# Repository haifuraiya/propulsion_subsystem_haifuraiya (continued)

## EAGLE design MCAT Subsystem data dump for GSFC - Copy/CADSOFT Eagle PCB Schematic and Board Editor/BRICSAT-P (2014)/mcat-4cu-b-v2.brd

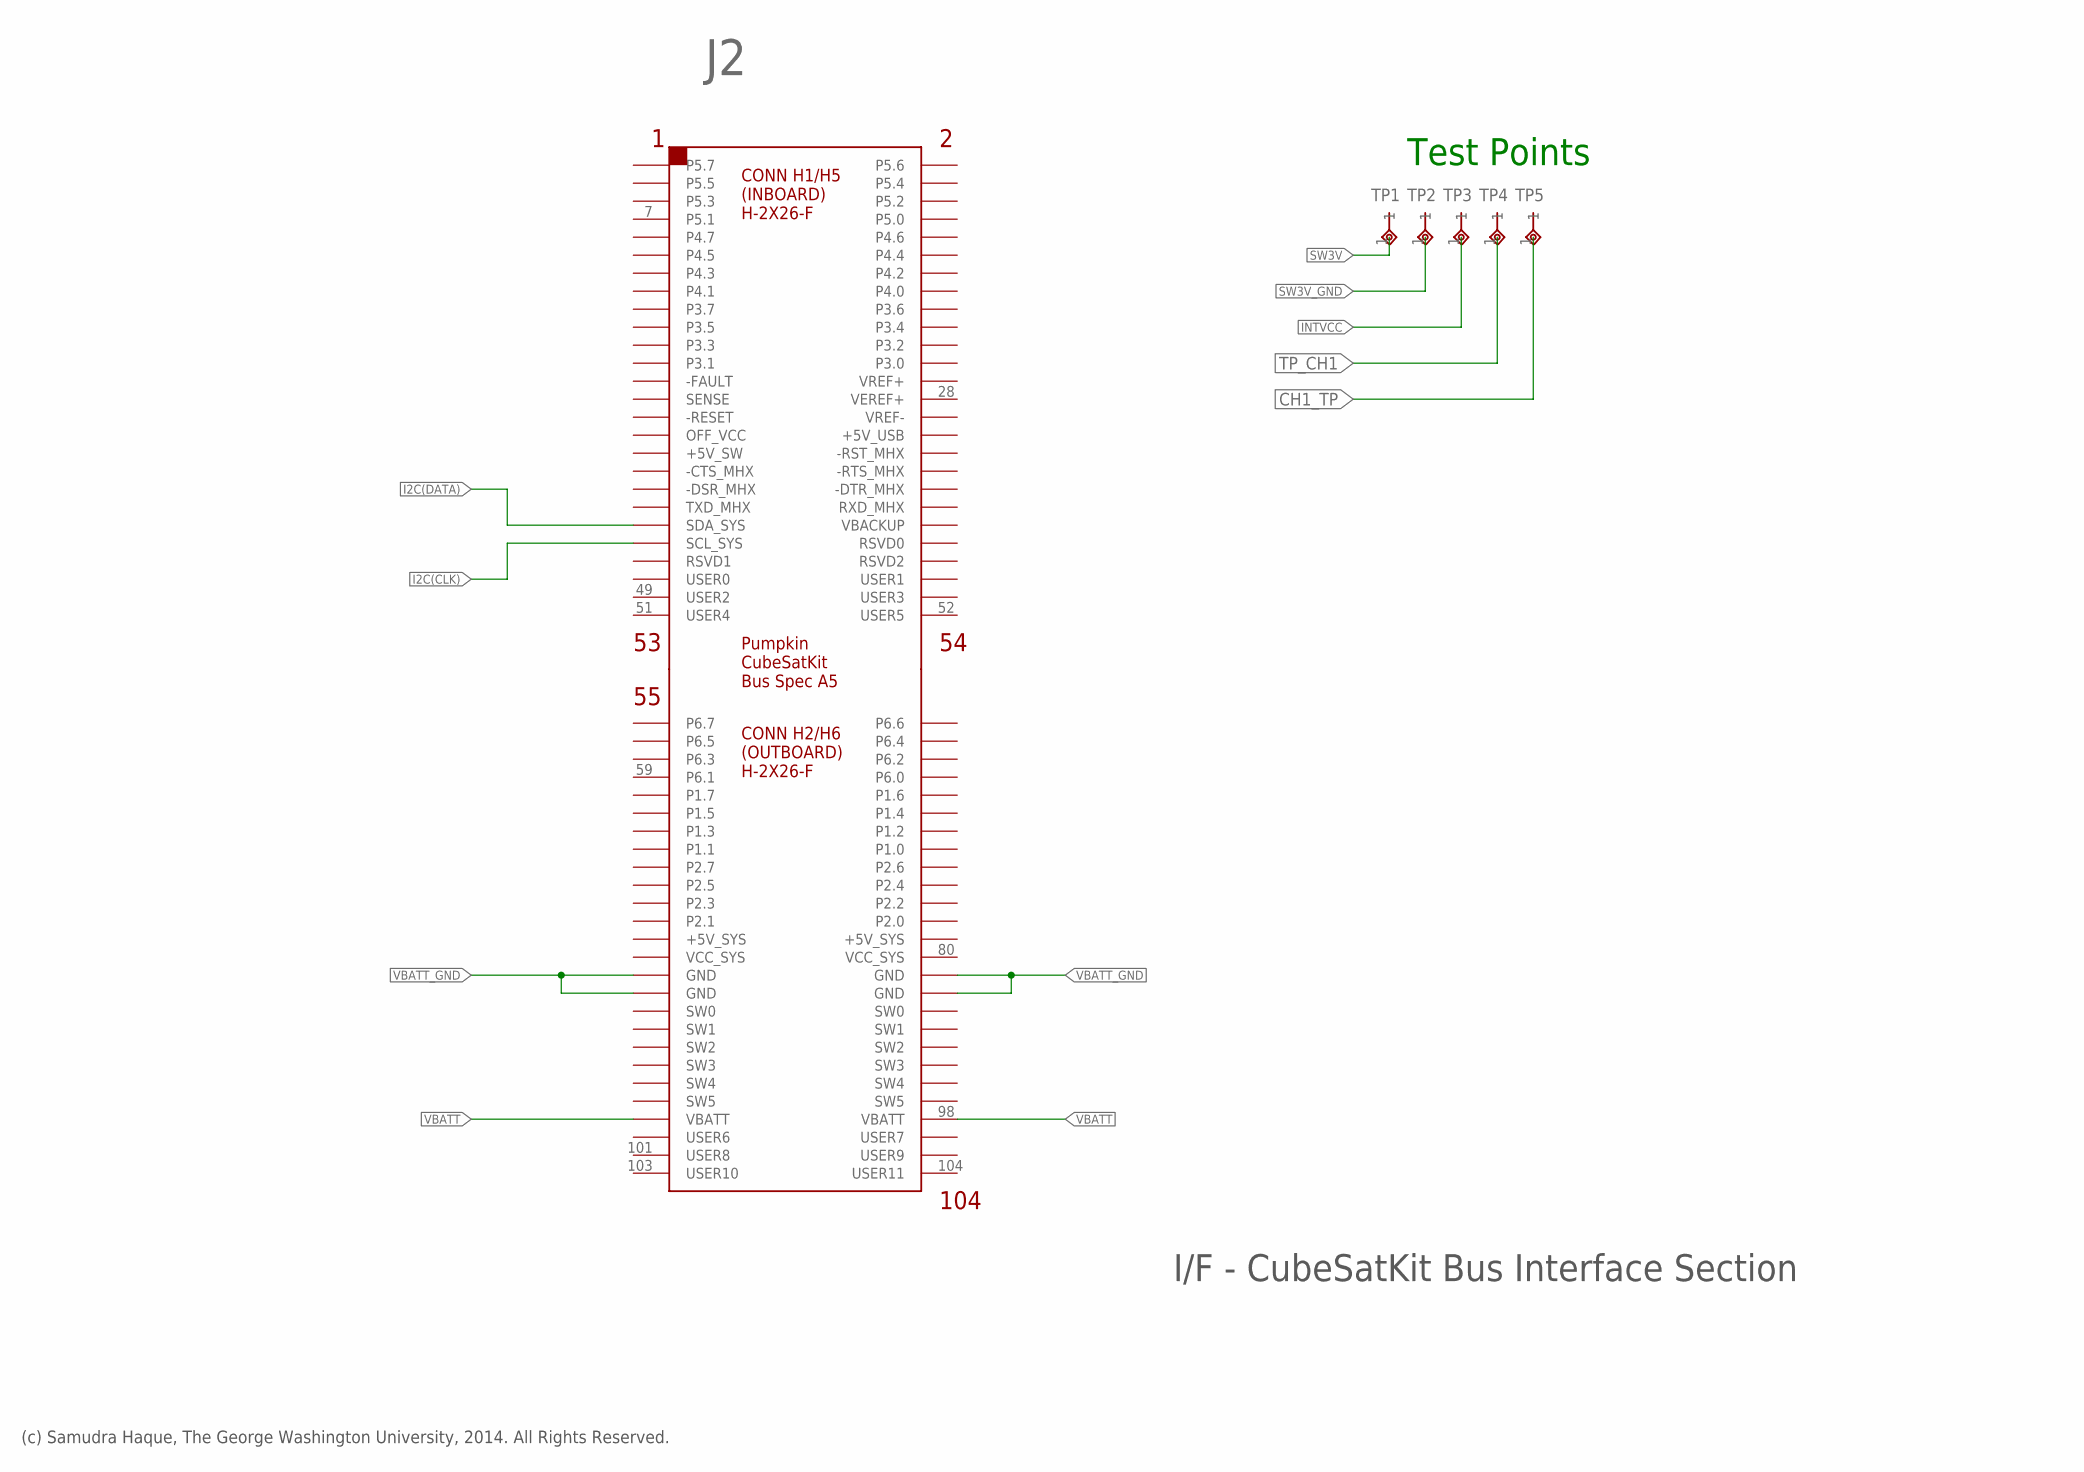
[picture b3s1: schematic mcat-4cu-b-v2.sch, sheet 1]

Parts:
J2: CSK-BUS-CONN2X2X26; CSK-BUS-PKG
TP1, TP2, TP3, TP4, TP5: 1P-1508-0-57-15-00-00-03-0; 1P-TP-MILLMAX-11

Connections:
CH1_TP: TP5.1; also elsewhere on the board
I2C(CLK): J2.43 (SCL_SYS); also elsewhere on the board
I2C(DATA): J2.41 (SDA_SYS); also elsewhere on the board
INTVCC: TP3.1; also elsewhere on the board
SW3V: TP1.1; also elsewhere on the board
SW3V_GND: TP2.1; also elsewhere on the board
TP_CH1: TP4.1; also elsewhere on the board
VBATT: J2.97 (VBATT), J2.98 (VBATT); also elsewhere on the board
VBATT_GND: J2.81 (GND), J2.82 (GND), J2.83 (GND), J2.84 (GND); also elsewhere on the board

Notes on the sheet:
I/F - CubeSatKit Bus Interface Section
Test Points
(c) Samudra Haque, The George Washington University, 2014. All Rights Reserved.

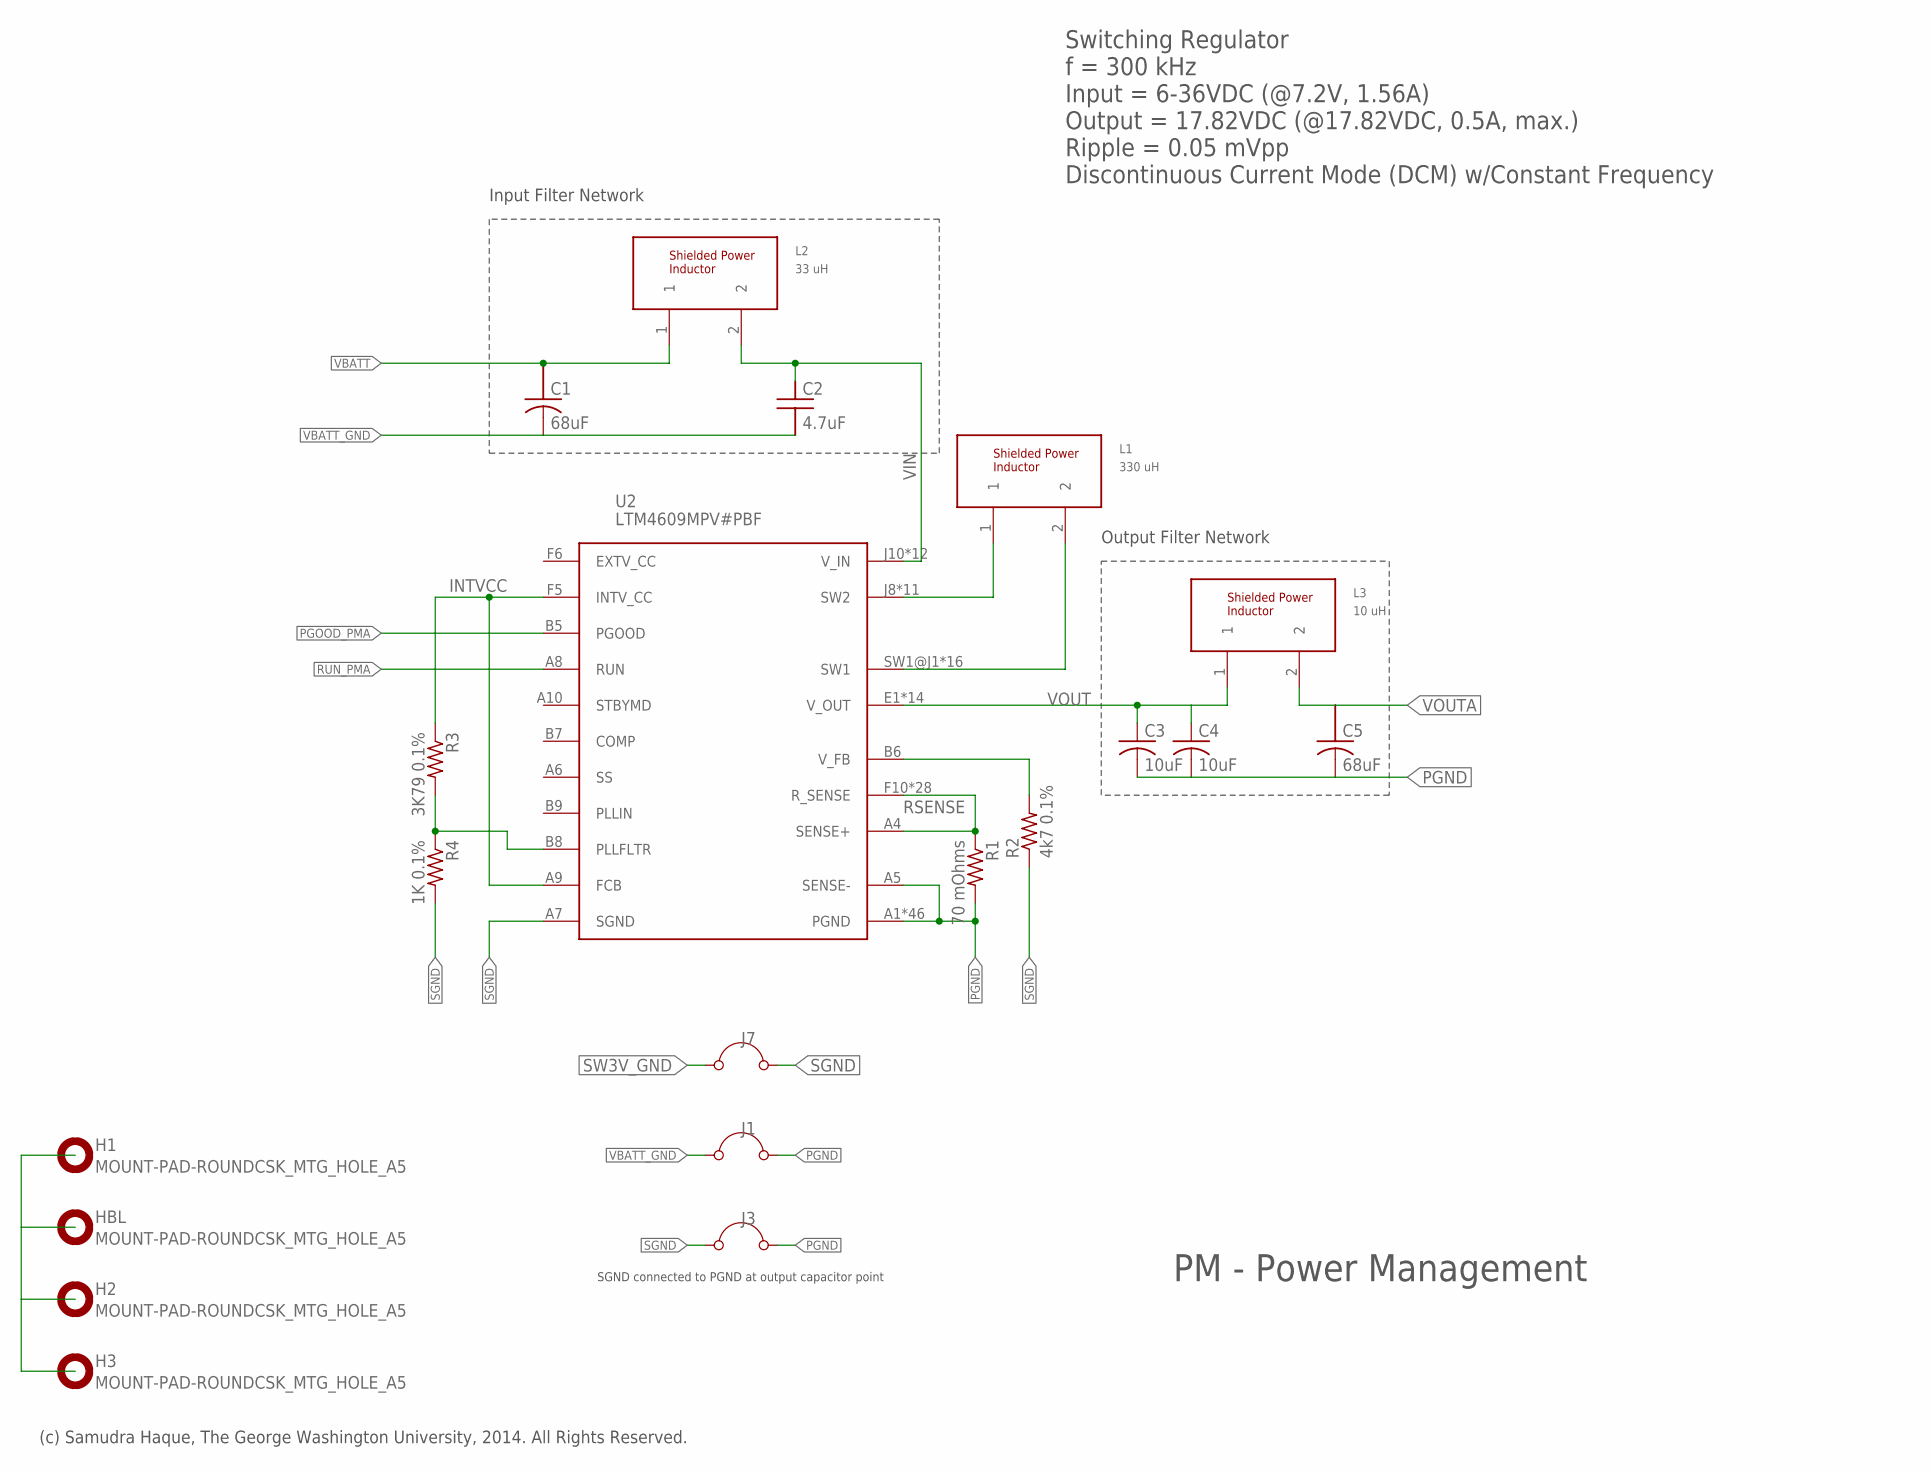
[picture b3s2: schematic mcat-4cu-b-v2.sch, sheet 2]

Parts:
C1, C5: 68uF; OS-CON-SVPF-F12
C2: 4.7uF; MLCC-X7R-1210
C3, C4: 10uF; C1210K
H1, H2, H3: MOUNT-PAD-ROUNDCSK_MTG_HOLE_A5; CSK_MOUNTING_HOLE
HBL: MOUNT-PAD-ROUNDCSK_MTG_HOLE_A5; CSK_MOUNTING_HOLE
J1, J3, J7: JUMPER; 05
L1: 330 uH; MSS1048
L2: 33 uH; MSS1048
L3: 10 uH; SERIES-POWER-INDUCTORS
R1: 70 mOhms; R1206
R2: 4k7 0.1%; R0603
R3: 3K79 0.1%; R0805
R4: 1K 0.1%; R0805
U2: LTM4609MPV#PBF; LGA-141-LTC-05-08-1840-B

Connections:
INTVCC: R3.1, U2.A9 (FCB), U2.F5 (INTV_CC); also elsewhere on the board
unnamed: R2.2, U2.B6 (V_FB)
unnamed: H1.P$1, H2.P$1, H3.P$1, HBL.P$1
PGND: C3.2, C4.2, C5.K1 (K), J1.2 (-), J3.2 (-), R1.2, U2.A1 (PGND), U2.A2 (PGND), U2.A3 (PGND), U2.A5 (SENSE-), U2.A11 (PGND), U2.A12 (PGND), U2.B1 (PGND), U2.B2 (PGND), U2.B3 (PGND), U2.B4 (PGND), U2.B10 (PGND), U2.B11 (PGND), U2.B12 (PGND), U2.C1 (PGND), U2.C2 (PGND), U2.C3 (PGND), U2.C4 (PGND), U2.C5 (PGND), U2.C6 (PGND), U2.C7 (PGND), U2.C8 (PGND), U2.C9 (PGND), U2.C10 (PGND), U2.C11 (PGND), U2.C12 (PGND), U2.D1 (PGND), U2.D2 (PGND), U2.D3 (PGND), U2.D4 (PGND), U2.D5 (PGND), U2.D6 (PGND), U2.D7 (PGND), U2.D8 (PGND), U2.D9 (PGND), U2.D10 (PGND), U2.D11 (PGND), U2.D12 (PGND), U2.E3 (PGND), U2.E4 (PGND), U2.E5 (PGND), U2.E6 (PGND), U2.E7 (PGND), U2.E8 (PGND), U2.E9 (PGND), U2.E10 (PGND), U2.E11 (PGND), U2.E12 (PGND); also elsewhere on the board
PGOOD_PMA: U2.B5 (PGOOD)
RSENSE: R1.1, U2.A4 (SENSE+), U2.F10 (R_SENSE), U2.F11 (R_SENSE), U2.F12 (R_SENSE), U2.G5 (R_SENSE), U2.G6 (R_SENSE), U2.G7 (R_SENSE), U2.G8 (R_SENSE), U2.G9 (R_SENSE), U2.G10 (R_SENSE), U2.G11 (R_SENSE), U2.G12 (R_SENSE), U2.H5 (R_SENSE), U2.H6 (R_SENSE), U2.H7 (R_SENSE), U2.H8 (R_SENSE), U2.H9 (R_SENSE), U2.H10 (R_SENSE), U2.H11 (R_SENSE), U2.H12 (R_SENSE), U2.J5 (R_SENSE), U2.J6 (R_SENSE), U2.J7 (R_SENSE), U2.K5 (R_SENSE), U2.K6 (R_SENSE), U2.L5 (R_SENSE), U2.L6 (R_SENSE), U2.M5 (R_SENSE), U2.M6 (R_SENSE)
RUN_PMA: U2.A8 (RUN)
SETFREQ: R3.2, R4.1, U2.B8 (PLLFLTR)
SGND: J3.1 (+), J7.2 (-), R2.1, R4.2, U2.A7 (SGND); also elsewhere on the board
SW1: L1.2, U2.SW1@J1 (SW1), U2.SW1@J2 (SW1), U2.SW1@J3 (SW1), U2.SW1@J4 (SW1), U2.SW1@K1 (SW1), U2.SW1@K2 (SW1), U2.SW1@K3 (SW1), U2.SW1@K4 (SW1), U2.SW1@L1 (SW1), U2.SW1@L2 (SW1), U2.SW1@L3 (SW1), U2.SW1@L4 (SW1), U2.SW1@M1 (SW1), U2.SW1@M2 (SW1), U2.SW1@M3 (SW1), U2.SW1@M4 (SW1)
SW2: L1.1, U2.J8 (SW2), U2.J9 (SW2), U2.K7 (SW2), U2.K8 (SW2), U2.K9 (SW2), U2.L7 (SW2), U2.L8 (SW2), U2.L9 (SW2), U2.M7 (SW2), U2.M8 (SW2), U2.M9 (SW2)
SW3V_GND: J7.1 (+); also elsewhere on the board
VBATT: C1.A1 (A), L2.1; also elsewhere on the board
VBATT_GND: C1.K1 (K), C2.2, J1.1 (+); also elsewhere on the board
VIN: C2.1, L2.2, U2.J10 (V_IN), U2.J11 (V_IN), U2.J12 (V_IN), U2.K10 (V_IN), U2.K11 (V_IN), U2.K12 (V_IN), U2.L10 (V_IN), U2.L11 (V_IN), U2.L12 (V_IN), U2.M10 (V_IN), U2.M11 (V_IN), U2.M12 (V_IN)
VOUT: C3.1, C4.1, L3.1, U2.E1 (V_OUT), U2.E2 (V_OUT), U2.F1 (V_OUT), U2.F2 (V_OUT), U2.F3 (V_OUT), U2.F4 (V_OUT), U2.G1 (V_OUT), U2.G2 (V_OUT), U2.G3 (V_OUT), U2.G4 (V_OUT), U2.H2 (V_OUT), U2.H3 (V_OUT), U2.H4 (V_OUT), U2.VOUT (V_OUT)
VOUTA: C5.A1 (A), L3.2; also elsewhere on the board

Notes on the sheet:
PM - Power Management
Input Filter Network
SGND connected to PGND at output capacitor point
Output Filter Network
Switching Regulator f = 300 kHz Input = 6-36VDC (@7.2V, 1.56A) Output = 17.82VDC (@17.82VDC, 0.5A, max.) Ripple = 0.05 mVpp Discontinuous Current Mode (DCM) w/Constant Frequency
(c) Samudra Haque, The George Washington University, 2014. All Rights Reserved.

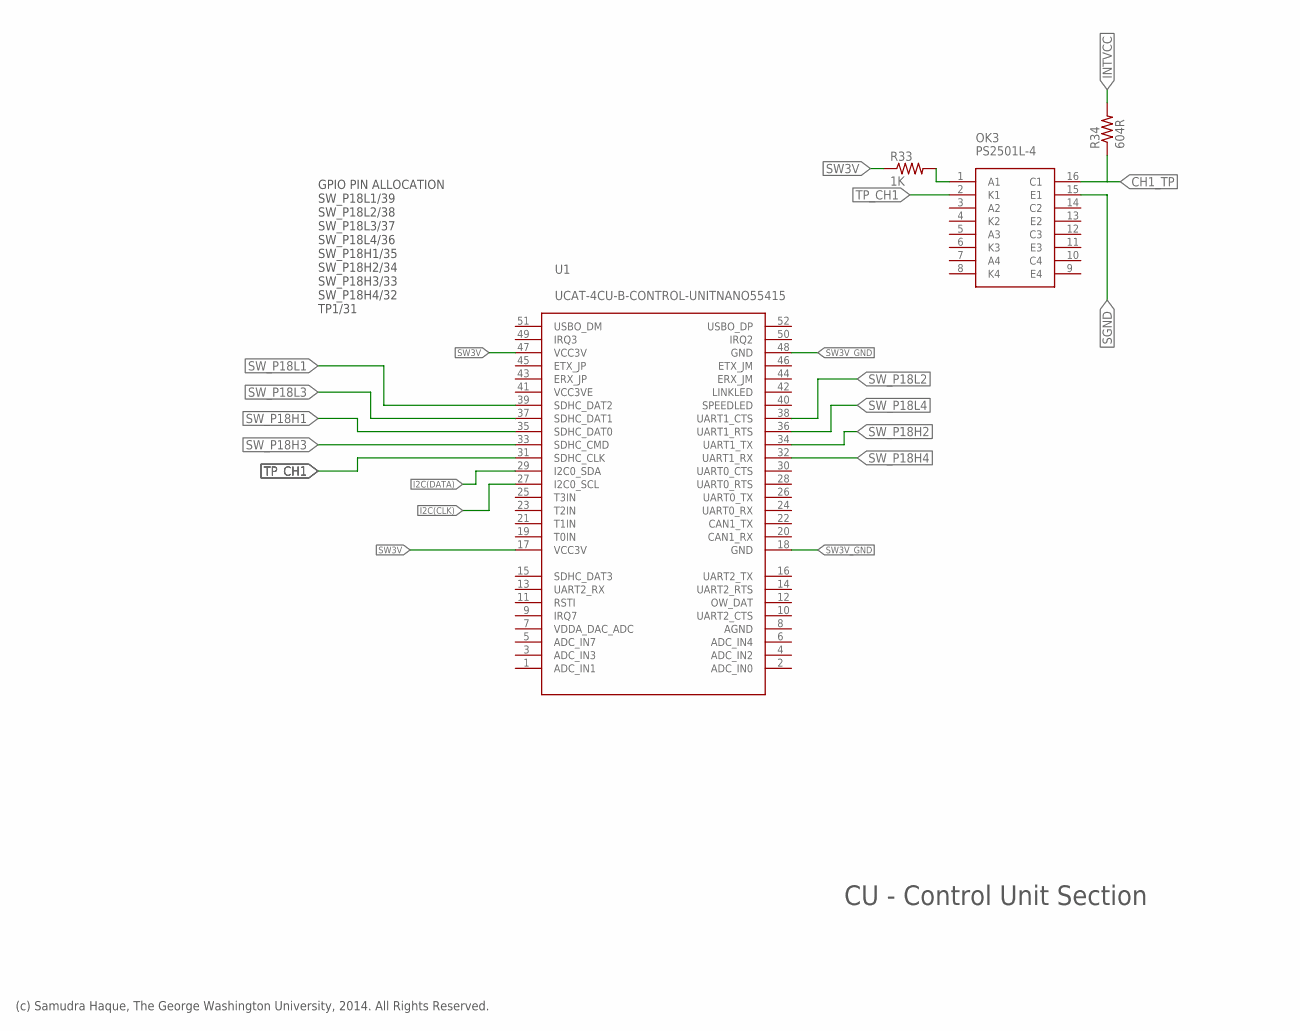
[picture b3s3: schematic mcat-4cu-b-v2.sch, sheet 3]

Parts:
OK3: PS2501L-4
R33: 1K; R0805
R34: 604R; R0805
U1: UCAT-4CU-B-CONTROL-UNITNANO55415; MOLEX-MINI-PCI-EXPRESS-8MM-52CKT

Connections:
CH1_TP: OK3.16 (C1), R34.1; also elsewhere on the board
I2C(CLK): U1.27 (I2C0_SCL); also elsewhere on the board
I2C(DATA): U1.29 (I2C0_SDA); also elsewhere on the board
INTVCC: R34.2; also elsewhere on the board
unnamed: OK3.1 (A1), R33.2
SGND: OK3.15 (E1); also elsewhere on the board
SW3V: R33.1, U1.17 (VCC3V), U1.47 (VCC3V); also elsewhere on the board
SW3V_GND: U1.48 (GND); also elsewhere on the board
SW_P18H1: U1.35 (SDHC_DAT0); also elsewhere on the board
SW_P18H2: U1.34 (UART1_TX); also elsewhere on the board
SW_P18H3: U1.33 (SDHC_CMD); also elsewhere on the board
SW_P18H4: U1.32 (UART1_RX); also elsewhere on the board
SW_P18L1: U1.39 (SDHC_DAT2); also elsewhere on the board
SW_P18L2: U1.38 (UART1_CTS); also elsewhere on the board
SW_P18L3: U1.37 (SDHC_DAT1); also elsewhere on the board
SW_P18L4: U1.36 (UART1_RTS); also elsewhere on the board
TP_CH1: OK3.2 (K1), U1.31 (SDHC_CLK); also elsewhere on the board

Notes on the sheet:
CU - Control Unit Section
GPIO PIN ALLOCATION SW_P18L1/39 SW_P18L2/38 SW_P18L3/37 SW_P18L4/36 SW_P18H1/35 SW_P18H2/34 SW_P18H3/33 SW_P18H4/32 TP1/31
(c) Samudra Haque, The George Washington University, 2014. All Rights Reserved.

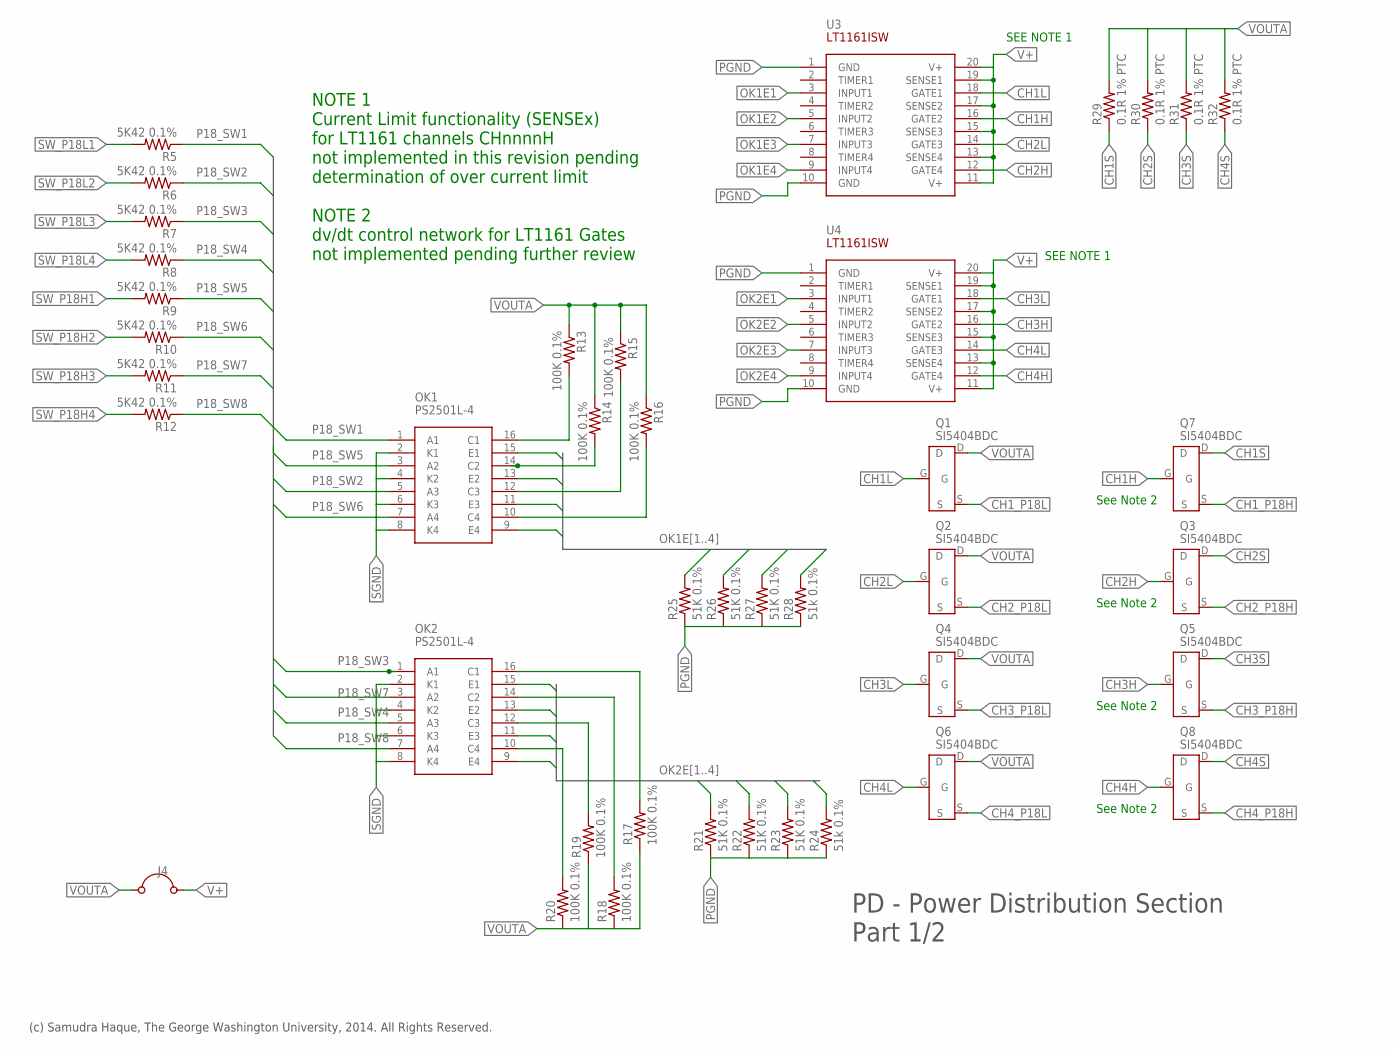
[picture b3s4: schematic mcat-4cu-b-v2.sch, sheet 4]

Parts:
J4: JUMPER; 05
OK1, OK2: PS2501L-4
Q1, Q2, Q3, Q4, Q5, Q6, Q7, Q8: SI5404BDC; 1206-8-CHIPFET
R5, R6, R7, R8, R9, R10, R11, R12: 5K42 0.1%; R1206
R13, R14, R15, R16, R17, R18, R19, R20: 100K 0.1%; R0402
R21, R22, R23, R25, R26, R27: 51K 0.1%; R0603
R24, R28: 51k 0.1%; R0603
R29, R30, R31, R32: 0.1R 1% PTC; R0402
U3, U4: LT1161ISW; 20-LEAD-PLASTIC-SO

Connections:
CH1H: Q7.G, U3.16 (GATE2)
CH1L: Q1.G, U3.18 (GATE1)
CH1S: Q7.D, R29.1
CH1_P18H: Q7.S; also elsewhere on the board
CH1_P18L: Q1.S; also elsewhere on the board
CH2H: Q3.G, U3.12 (GATE4)
CH2L: Q2.G, U3.14 (GATE3)
CH2S: Q3.D, R30.1
CH2_P18H: Q3.S; also elsewhere on the board
CH2_P18L: Q2.S; also elsewhere on the board
CH3H: Q5.G, U4.16 (GATE2)
CH3L: Q4.G, U4.18 (GATE1)
CH3S: Q5.D, R31.1
CH3_P18H: Q5.S; also elsewhere on the board
CH3_P18L: Q4.S; also elsewhere on the board
CH4H: Q8.G, U4.12 (GATE4)
CH4L: Q6.G, U4.14 (GATE3)
CH4S: Q8.D, R32.1
CH4_P18H: Q8.S; also elsewhere on the board
CH4_P18L: Q6.S; also elsewhere on the board
unnamed: OK1.16 (C1), R13.2
unnamed: OK1.14 (C2), R14.2
unnamed: OK1.12 (C3), R15.2
unnamed: OK1.10 (C4), R16.2
unnamed: OK2.16 (C1), R17.2
unnamed: OK2.14 (C2), R18.2
unnamed: OK2.12 (C3), R19.2
unnamed: OK2.10 (C4), R20.2
OK1E1: OK1.15 (E1), R25.2, U3.3 (INPUT1)
OK1E2: OK1.13 (E2), R26.2, U3.5 (INPUT2)
OK1E3: OK1.11 (E3), R27.2, U3.7 (INPUT3)
OK1E4: OK1.9 (E4), R28.2, U3.9 (INPUT4)
OK2E1: OK2.15 (E1), R21.2, U4.3 (INPUT1)
OK2E2: OK2.13 (E2), R22.2, U4.5 (INPUT2)
OK2E3: OK2.11 (E3), R23.2, U4.7 (INPUT3)
OK2E4: OK2.9 (E4), R24.2, U4.9 (INPUT4)
P18_SW1: OK1.1 (A1), R5.1
P18_SW2: OK1.5 (A3), R6.1
P18_SW3: OK2.1 (A1), R7.1
P18_SW4: OK2.5 (A3), R8.1
P18_SW5: OK1.3 (A2), R9.1
P18_SW6: OK1.7 (A4), R10.1
P18_SW7: OK2.3 (A2), R11.1
P18_SW8: OK2.7 (A4), R12.1
PGND: R21.1, R22.1, R23.1, R24.1, R25.1, R26.1, R27.1, R28.1, U3.1 (GND), U3.10 (GND), U4.1 (GND), U4.10 (GND); also elsewhere on the board
SGND: OK1.2 (K1), OK1.4 (K2), OK1.6 (K3), OK1.8 (K4), OK2.2 (K1), OK2.4 (K2), OK2.6 (K3), OK2.8 (K4); also elsewhere on the board
SW_P18H1: R9.2; also elsewhere on the board
SW_P18H2: R10.2; also elsewhere on the board
SW_P18H3: R11.2; also elsewhere on the board
SW_P18H4: R12.2; also elsewhere on the board
SW_P18L1: R5.2; also elsewhere on the board
SW_P18L2: R6.2; also elsewhere on the board
SW_P18L3: R7.2; also elsewhere on the board
SW_P18L4: R8.2; also elsewhere on the board
V+: J4.2 (-), U3.11 (V+), U3.13 (SENSE4), U3.15 (SENSE3), U3.17 (SENSE2), U3.19 (SENSE1), U3.20 (V+), U4.11 (V+), U4.13 (SENSE4), U4.15 (SENSE3), U4.17 (SENSE2), U4.19 (SENSE1), U4.20 (V+)
VOUTA: J4.1 (+), Q1.D, Q2.D, Q4.D, Q6.D, R13.1, R14.1, R15.1, R16.1, R17.1, R18.1, R19.1, R20.1, R29.2, R30.2, R31.2, R32.2; also elsewhere on the board

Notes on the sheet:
PD - Power Distribution Section Part 1/2
NOTE 1 Current Limit functionality (SENSEx) for LT1161 channels CHnnnnH not implemented in this revision pending determination of over current limit NOTE 2 dv/dt control network for LT1161 Gates not implemented pending further review
SEE NOTE 1
See Note 2
(c) Samudra Haque, The George Washington University, 2014. All Rights Reserved.

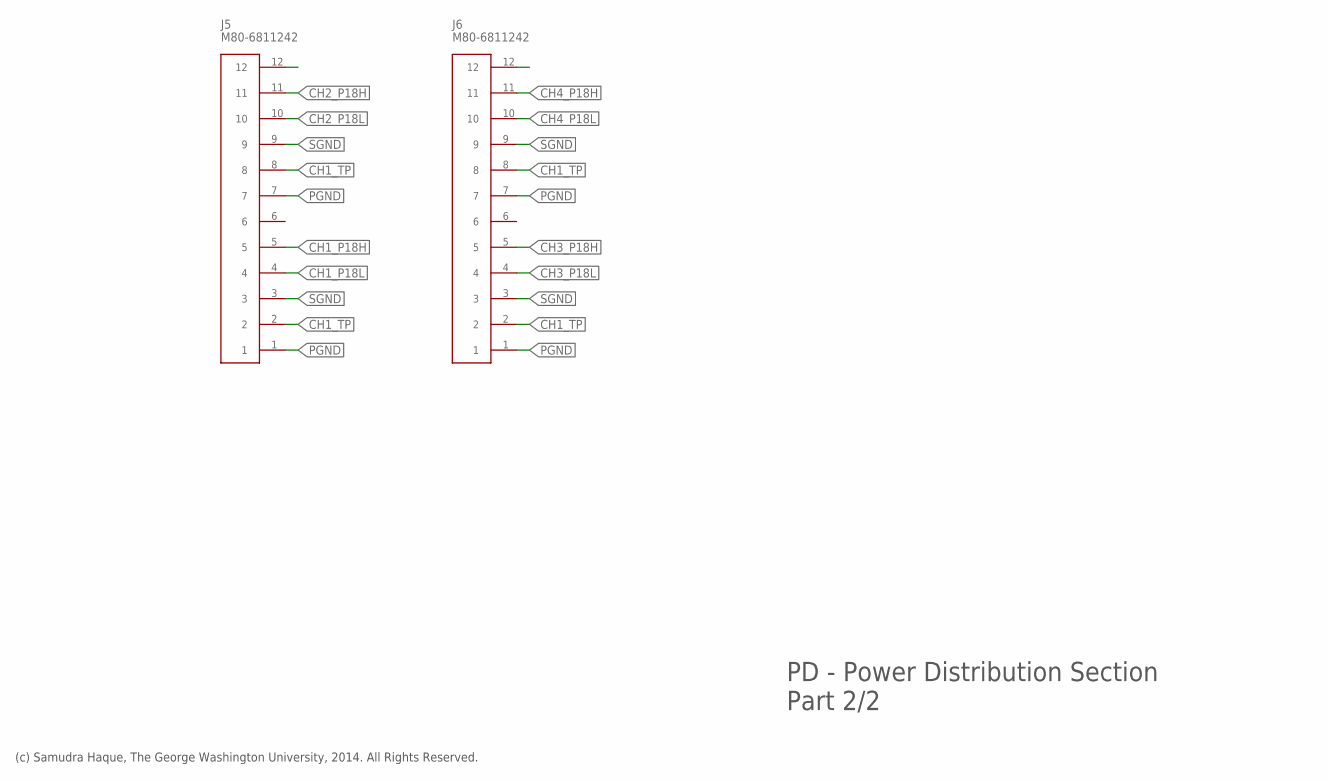
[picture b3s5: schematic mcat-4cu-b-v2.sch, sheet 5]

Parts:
J5, J6: M80-6811242; M80-68112

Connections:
CH1_P18H: J5.5; also elsewhere on the board
CH1_P18L: J5.4; also elsewhere on the board
CH1_TP: J5.2, J5.8, J6.2, J6.8; also elsewhere on the board
CH2_P18H: J5.11; also elsewhere on the board
CH2_P18L: J5.10; also elsewhere on the board
CH3_P18H: J6.5; also elsewhere on the board
CH3_P18L: J6.4; also elsewhere on the board
CH4_P18H: J6.11; also elsewhere on the board
CH4_P18L: J6.10; also elsewhere on the board
PGND: J5.1, J5.7, J6.1, J6.7; also elsewhere on the board
SGND: J5.3, J5.9, J6.3, J6.9; also elsewhere on the board

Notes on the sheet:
PD - Power Distribution Section Part 2/2
(c) Samudra Haque, The George Washington University, 2014. All Rights Reserved.

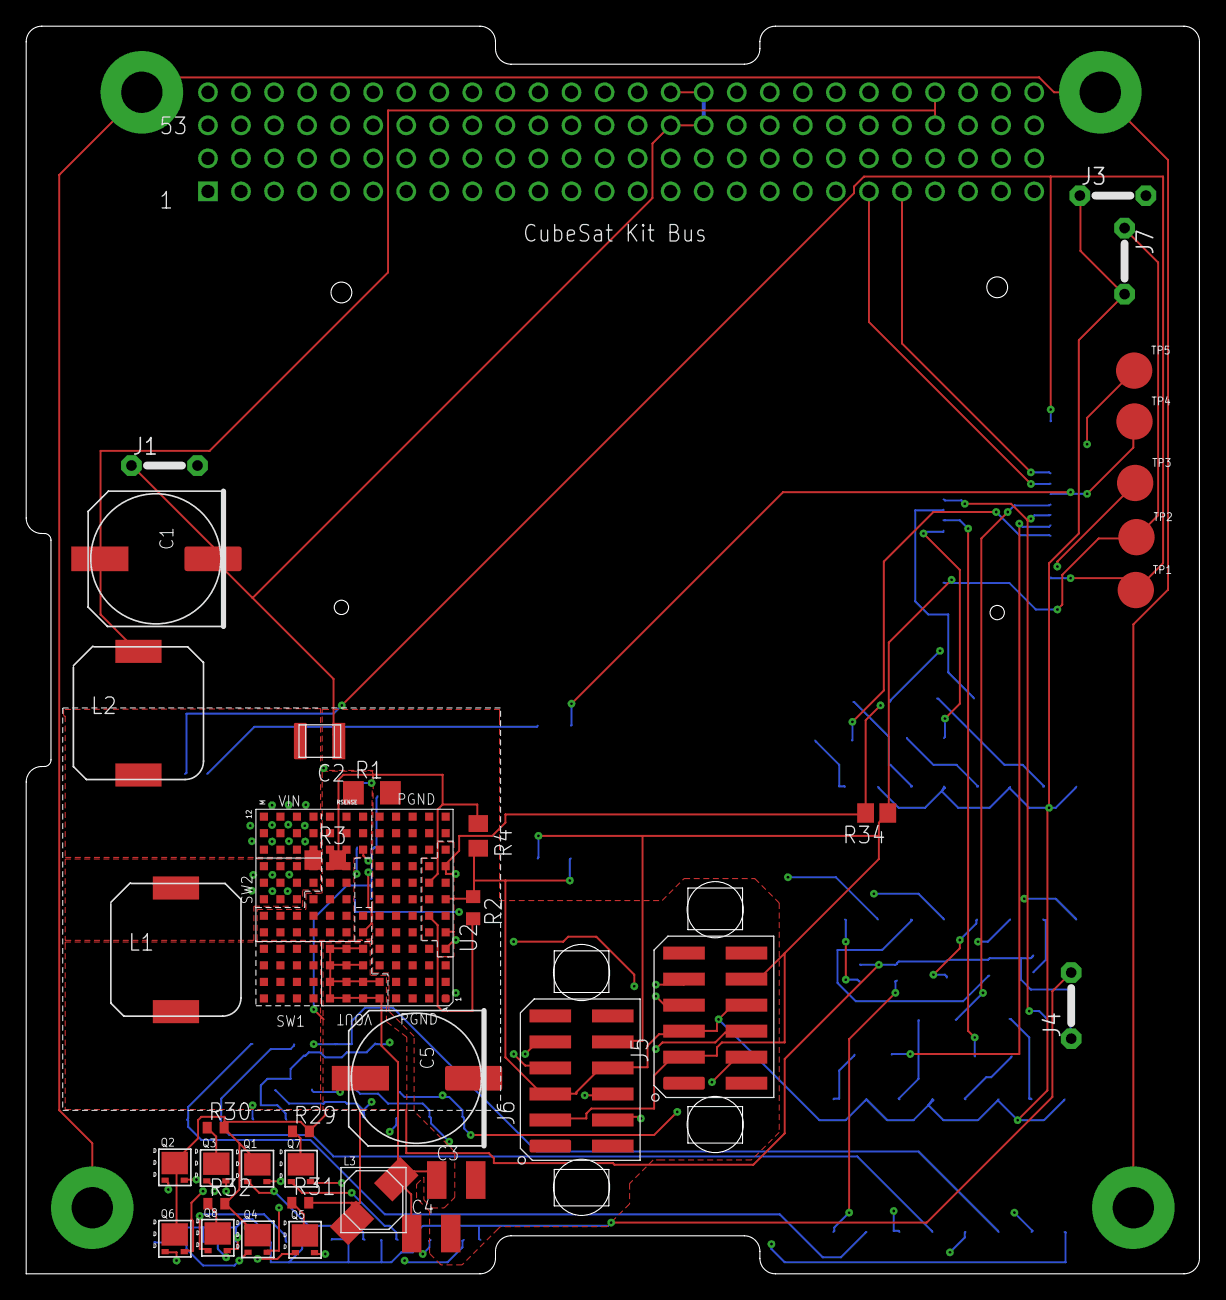
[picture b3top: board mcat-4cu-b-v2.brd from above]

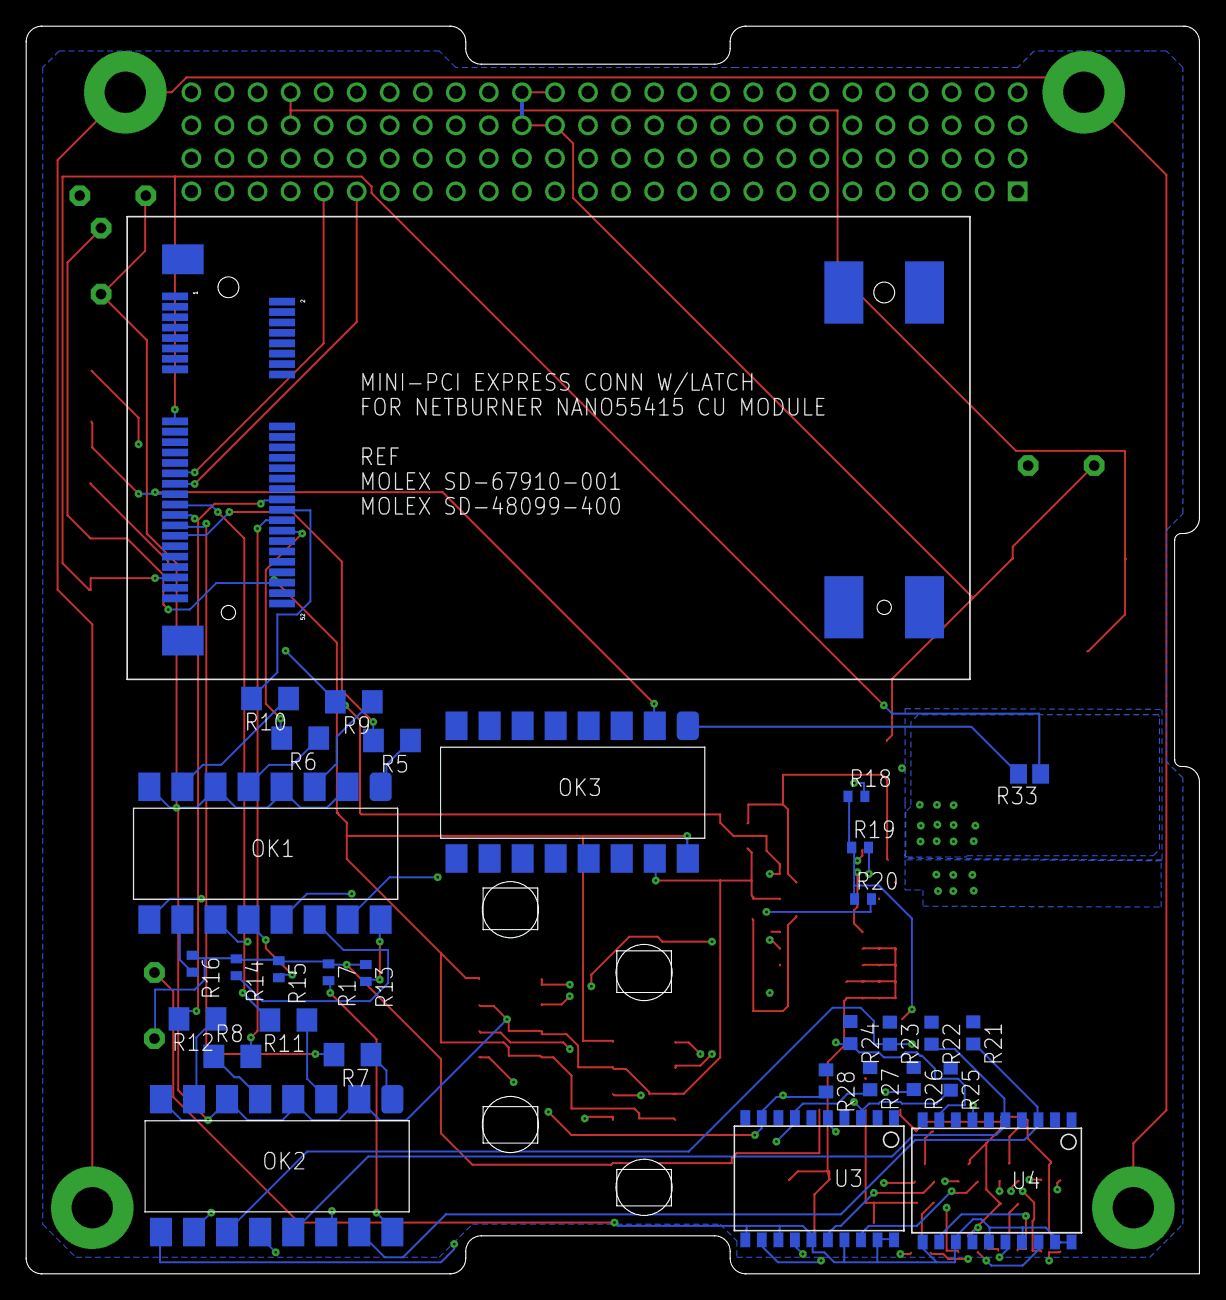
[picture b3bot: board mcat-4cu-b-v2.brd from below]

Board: 4 copper layers, 90.2 x 95.9 mm, 73 parts (31 on the bottom side), 74 nets.
